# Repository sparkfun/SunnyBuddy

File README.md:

Sunny Buddy - MPPT Solar Charger
================================

[*Sunny Buddy (PRT-12885)*](https://www.sparkfun.com/products/12885)

This is a maximum power point tracking solar charger for single-cell LiPo batteries. 

Repository Contents
-------------------
* **/Fritzing** - Fritzing Example wiring images
* **/Hardware** - All Eagle design files (.brd, .sch)
* **/Production** - Test bed files and production panel files

Documentation
--------------
* **[Hookup Guide](https://learn.sparkfun.com/tutorials/sunny-buddy-solar-charger-v13-hookup-guide)** - Basic hookup guide for the Sunny Buddy.

Product Versions
----------------
* [PRT-12885 ](https://www.sparkfun.com/products/12885 )- Version 1.3
* [PRT-12084](https://www.sparkfun.com/products/12084) - Version 1.0

Version History
---------------
* [v10](https://github.com/sparkfun/SunnyBuddy/tree/HW_V1.0) -GitHub files for v1.0

License Information
-------------------
The hardware is released under [Creative Commons ShareAlike 4.0 International](https://creativecommons.org/licenses/by-sa/4.0/).
The code is beerware; if you see me (or any other SparkFun employee) at the local, and you've found our code helpful, please buy us a round!

Distributed as-is; no warranty is given.

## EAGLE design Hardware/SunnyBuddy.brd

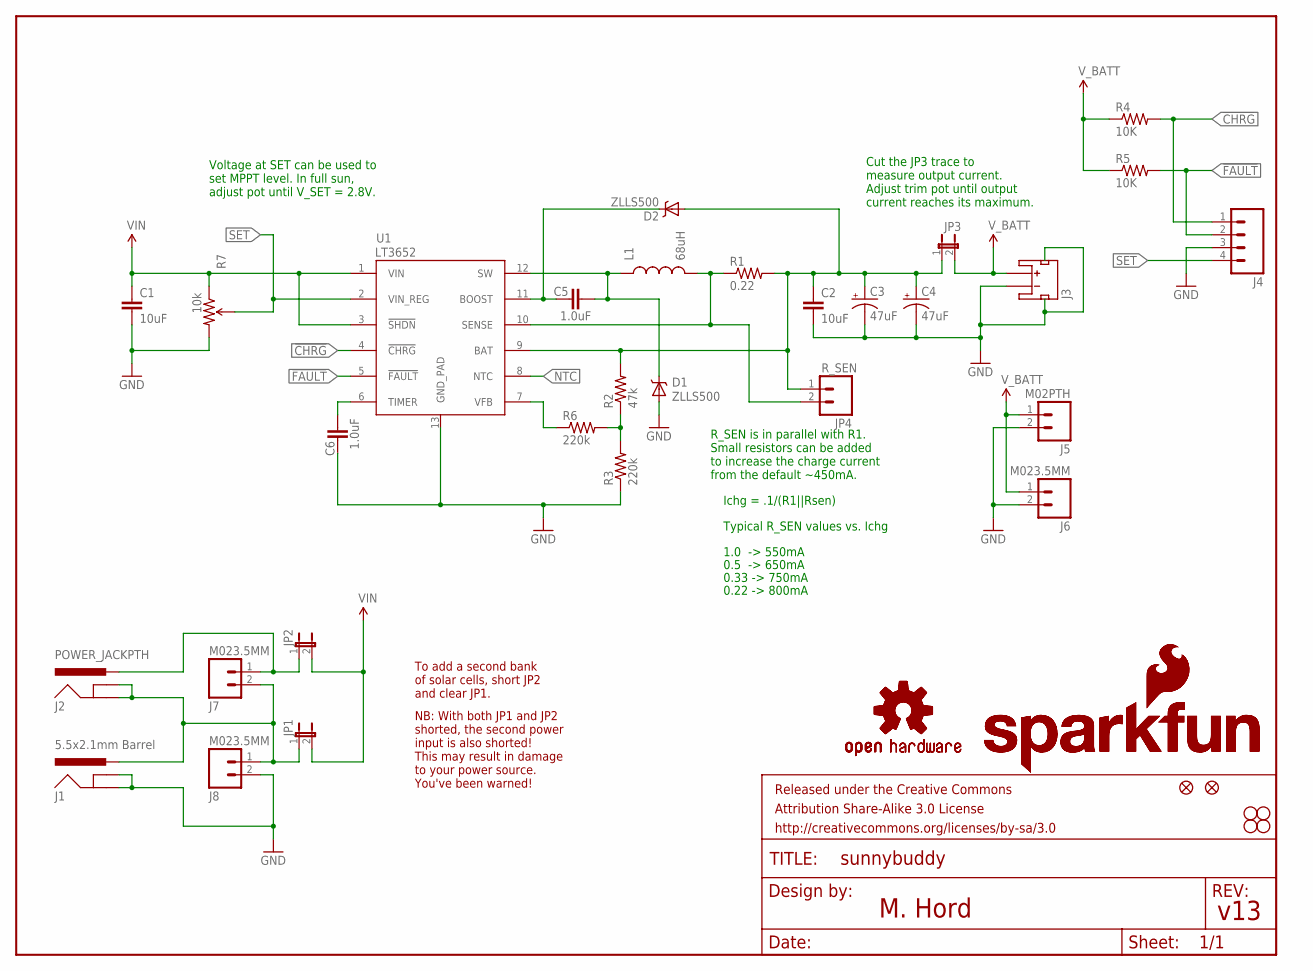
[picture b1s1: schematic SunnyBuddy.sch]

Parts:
C1: 10uF; 1210
C2: 10uF; 1206
C3, C4: 47uF; EIA3528
C5, C6: 1.0uF; 0603-CAP
D1, D2: ZLLS500; SOT23
FID1, FID2: FIDUCIAL1X2; FIDUCIAL-1X2
FRAME1: FRAME-LETTER; CREATIVE_COMMONS
J1: 5.5x2.1mm Barrel; POWER_JACK_SMD
J2: POWER_JACKPTH; POWER_JACK_PTH
J3: JST_2MM_MALE; JST-2-SMD
J4: M04PTH; 1X04
J5: M02PTH; 1X02
J6, J7, J8: M023.5MM; SCREWTERMINAL-3.5MM-2
JP1: JUMPER-2SMD-NC; SJ_2S
JP2: JUMPER-2SMD-NO; SJ_2S-NO
JP3: JUMPER-PTH-2-NC; PTH-JUMPER-NC_BOTTOM_NO_SILK
JP4: R_SEN; 1X02
L1: 68uH; CR75
LOGO1: SFE_LOGO_NAME_FLAME.2_INCH; SFE_LOGO_NAME_FLAME_.2
LOGO2: OSHW-LOGOM; OSHW-LOGO-M
LOGO3: OSHW-LOGOS; OSHW-LOGO-S
LOGO4: SFE_LOGO_NAME_FLAME.3_INCH; SFE_LOGO_NAME_FLAME_.3
R1: 0.22; 0805
R2: 47k; 0603-RES
R3, R6: 220k; 0603-RES
R4, R5: 10K; 0603-RES
R7: 10k; TRIMPOT-3MM
STANDOFF1, STANDOFF2, STANDOFF3, STANDOFF4: STAND-OFF
U1: LT3652; MSOP-12_GND

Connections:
!CHRG: J4.1, R4.2, U1.4 (!CHRG)
!FAULT: J4.2, R5.2, U1.5 (!FAULT)
BOOST: C5.1, D2.3 (C), U1.11 (BOOST)
FB: R2.1, R3.2, R6.2
GND: C1.2, C2.2, C3.C (-), C4.C (-), C6.1, D1.1 (A), J1.GND (GNDBREAK), J1.P$4 (GND), J3.1 (-), J3.NC1 (PAD1), J3.NC2 (PAD2), J4.3, J5.2, J6.2, J8.2, R3.1, R7.3 (CW), U1.13 (GND_PAD)
unnamed: R6.1, U1.7 (VFB)
unnamed: C2.1, C3.A (+), C4.A (+), D2.1 (A), JP3.1, JP4.1, R1.2, R2.2, U1.9 (BAT)
unnamed: J1.VIN0 (PWR), J2.GND, J2.GNDBREAK, J7.2, J8.1, JP1.1
NTC: U1.8 (NTC)
SENSE: JP4.2, L1.P$2 (2), R1.1, U1.10 (SENSE)
SET: J4.4, R7.2 (WIPER), U1.2 (VIN_REG)
SFSASDF: J2.PWR, J7.1, JP2.1
SW: C5.2, D1.3 (C), L1.P$1 (1), U1.12 (SW)
TIMER: C6.2, U1.6 (TIMER)
VIN: C1.1, JP1.2, JP2.2, R7.1 (CCW), U1.1 (VIN), U1.3 (!SHDN)
V_BATT: J3.2 (+), J5.1, J6.1, JP3.2, R4.1, R5.1

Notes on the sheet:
To add a second bank of solar cells, short JP2 and clear JP1.
NB: With both JP1 and JP2 shorted, the second power input is also shorted! This may result in damage to your power source. You've been warned!
v13
M. Hord
Cut the JP3 trace to measure output current. Adjust trim pot until output current reaches its maximum.
R_SEN is in parallel with R1. Small resistors can be added to increase the charge current from the default ~450mA.
0.22 -> 800mA
Ichg = .1/(R1||Rsen)
Typical R_SEN values vs. Ichg
1.0 -> 550mA
0.33 -> 750mA
0.5 -> 650mA
Voltage at SET can be used to set MPPT level. In full sun, adjust pot until V_SET = 2.8V.

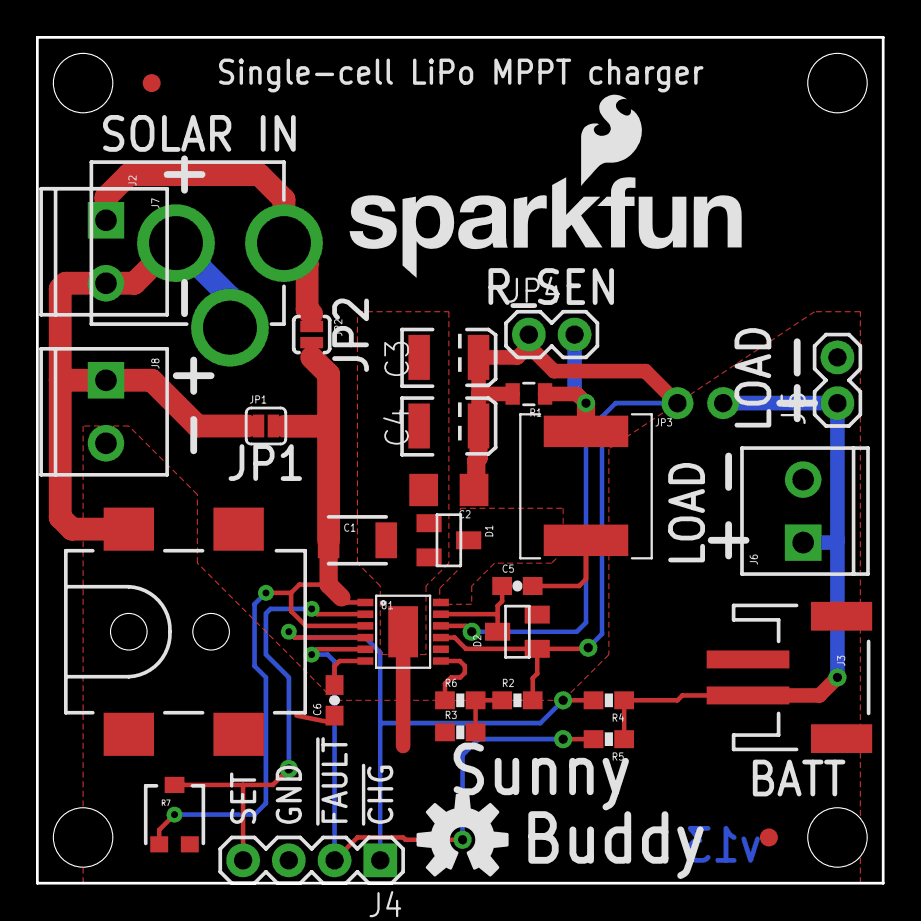
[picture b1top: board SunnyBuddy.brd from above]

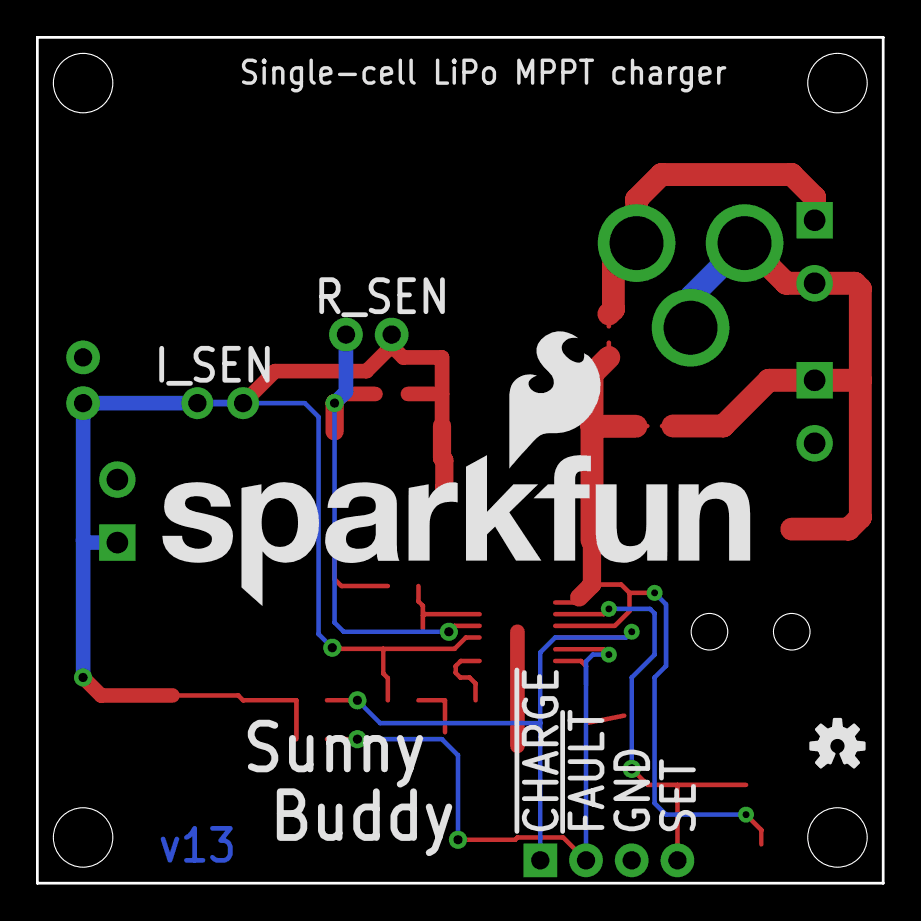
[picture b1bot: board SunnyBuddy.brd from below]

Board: 2 copper layers, 47.0 x 47.0 mm, 40 parts (2 on the bottom side), 15 nets.

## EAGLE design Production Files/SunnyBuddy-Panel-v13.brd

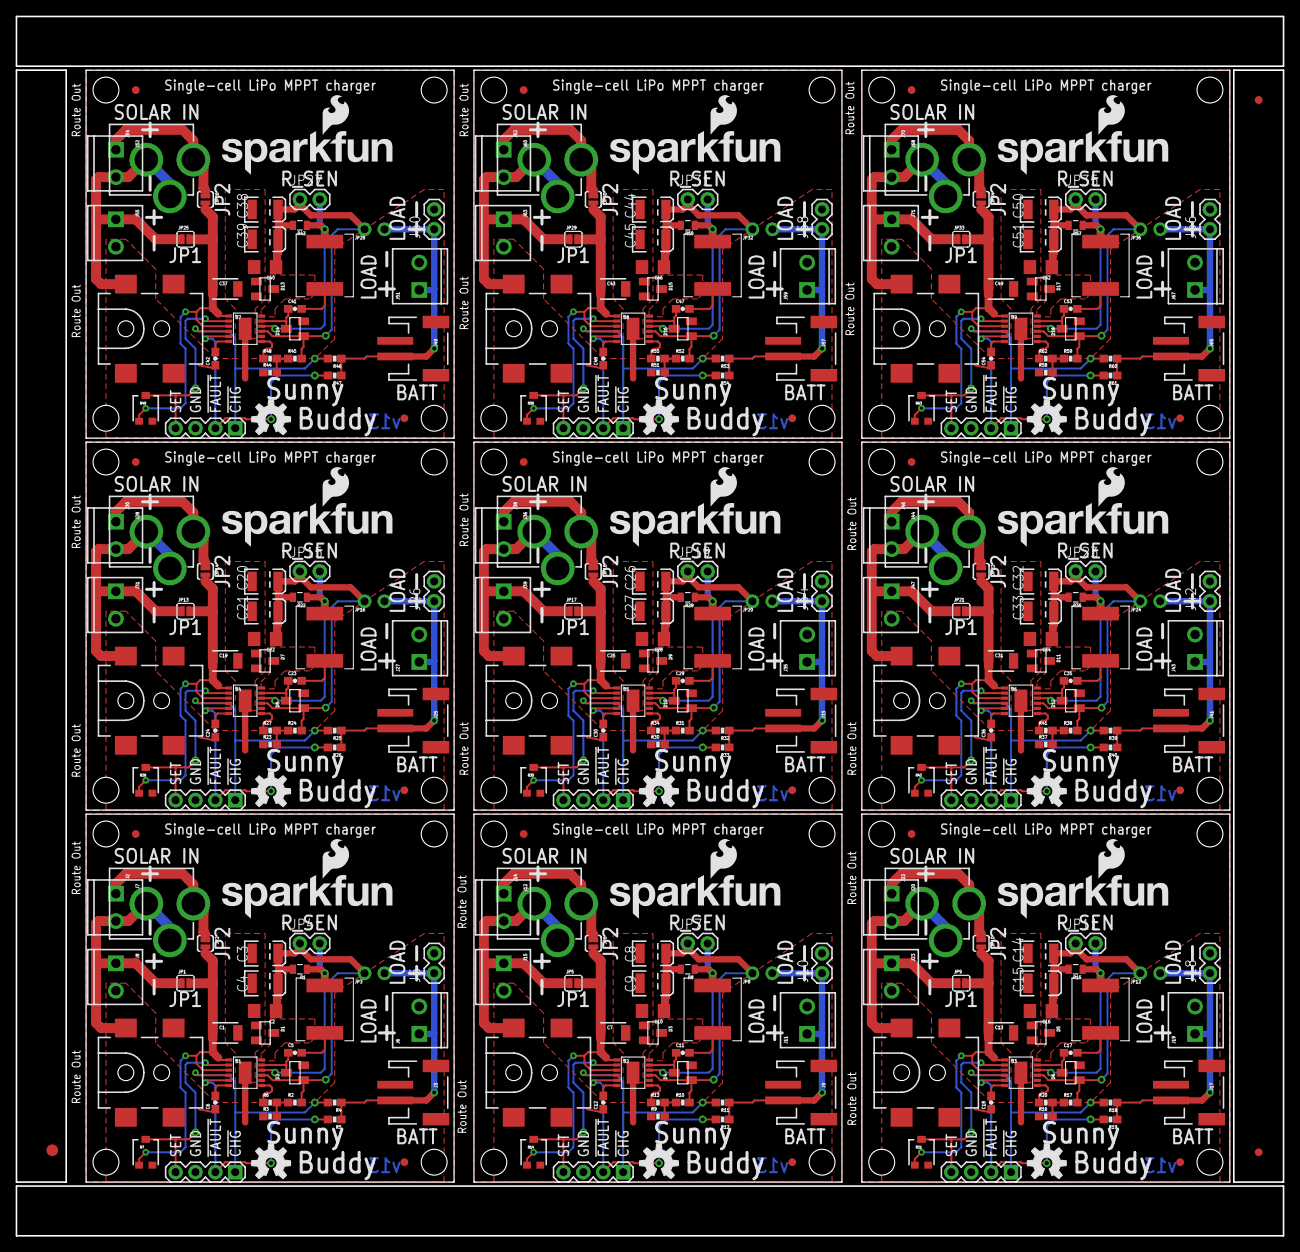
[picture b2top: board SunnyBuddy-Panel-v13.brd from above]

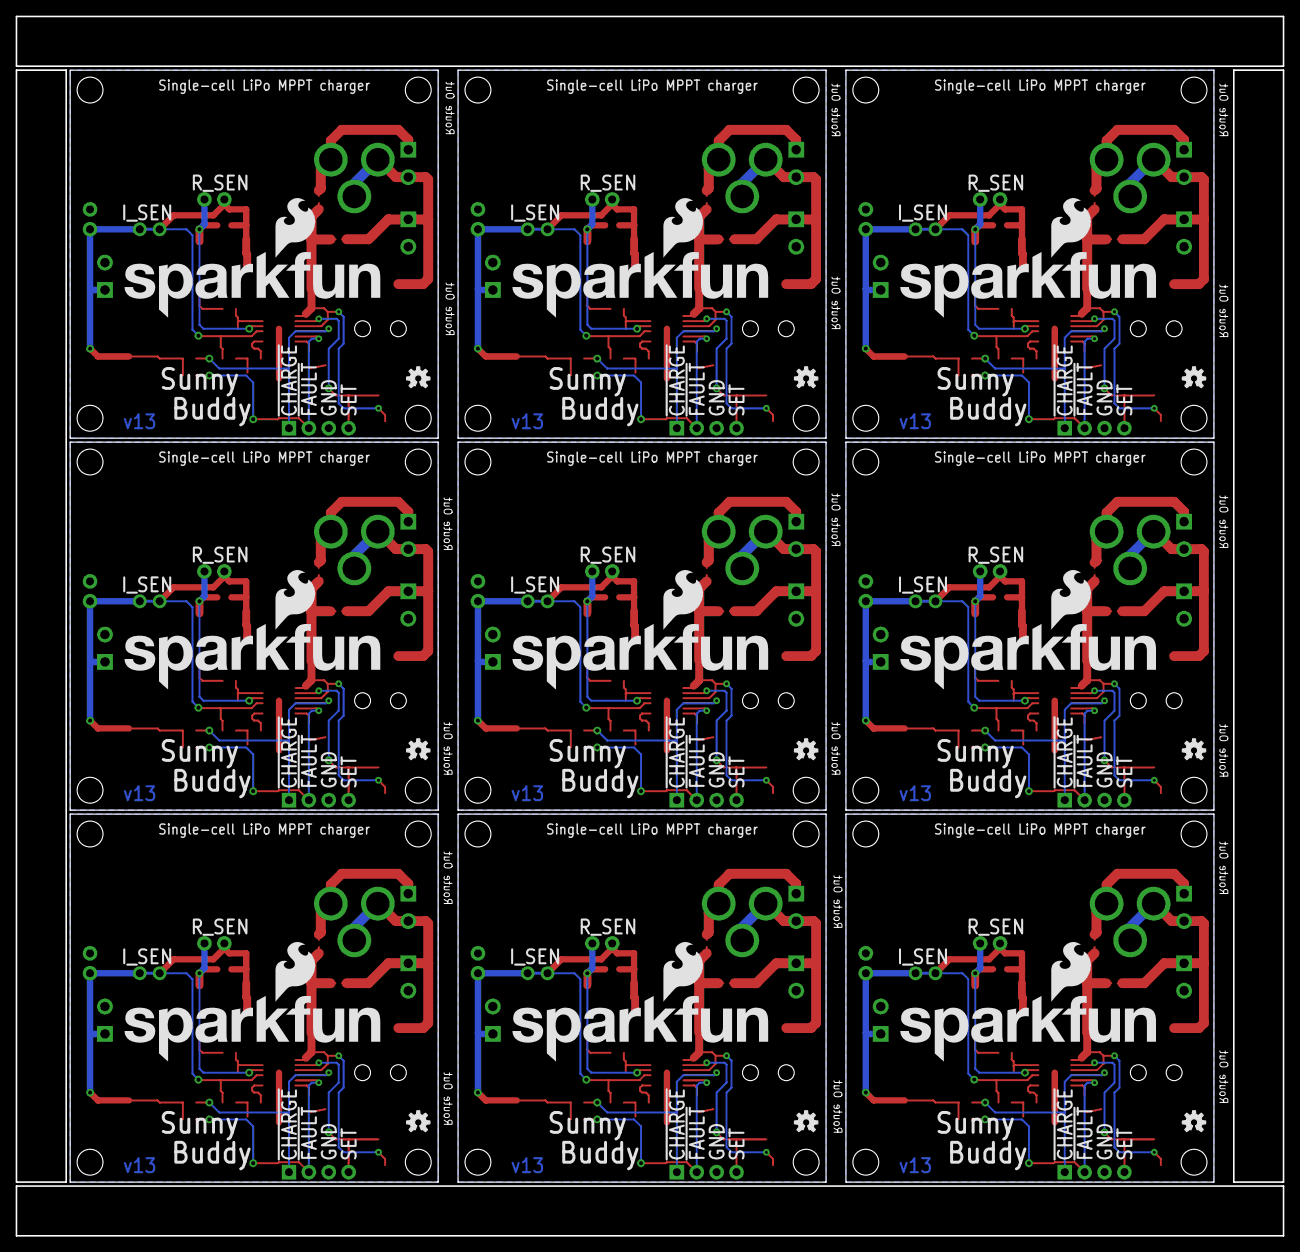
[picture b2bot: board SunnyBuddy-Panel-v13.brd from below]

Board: 2 copper layers, 161.8 x 155.7 mm, 354 parts (18 on the bottom side), 135 nets.

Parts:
C1, C7, C13, C19, C25, C31, C37, C43, C49: 10uF; 1210
C2, C10, C16, C22, C28, C34, C40, C46, C52: 10uF; 1206
C3, C4, C8, C9, C14, C15, C20, C21, C26, C27, C32, C33, C38, C39, C44, C45, C50, C51: 47uF; EIA3528
C5, C6, C11, C12, C17, C18, C23, C24, C29, C30, C35, C36, C41, C42, C47, C48, C53, C54: 1.0uF; 0603-CAP
D1, D2, D3, D4, D5, D6, D7, D8, D9, D10, D11, D12, D13, D14, D15, D16, D17, D18: ZLLS500; SOT23
E$1: FIDUCIAL-1.5X3
E$4, E$6: FIDUCIAL-1X2
FID1, FID2, FID3, FID4, FID5, FID6, FID7, FID8, FID9, FID10, FID11, FID12, FID13, FID14, FID15, FID16, FID17, FID18: FIDUCIAL1X2; FIDUCIAL-1X2
J1, J13, J21, J29, J37, J45, J53, J61, J69: 5.5x2.1mm Barrel; POWER_JACK_SMD
J2, J14, J22, J30, J38, J46, J54, J62, J70: POWER_JACKPTH; POWER_JACK_PTH
J3, J9, J17, J25, J33, J41, J49, J57, J65: JST-2-SMD
J4, J16, J24, J32, J40, J48, J56, J64, J72: 1X04
J5, J10, J18, J26, J34, J42, J50, J58, J66: M02PTH; 1X02
J6, J7, J8, J11, J12, J15, J19, J20, J23, J27, J28, J31, J35, J36, J39, J43, J44, J47, J51, J52, J55, J59, J60, J63, J67, J68, J71: M023.5MM; SCREWTERMINAL-3.5MM-2
JP1, JP5, JP9, JP13, JP17, JP21, JP25, JP29, JP33: SJ_2S
JP2, JP6, JP10, JP14, JP18, JP22, JP26, JP30, JP34: SJ_2S-NO
JP3, JP8, JP12, JP16, JP20, JP24, JP28, JP32, JP36: JUMPER-PTH-2-NC; PTH-JUMPER-NC_BOTTOM_NO_SILK
JP4, JP7, JP11, JP15, JP19, JP23, JP27, JP31, JP35: R_SEN; 1X02
L1, L2, L3, L4, L5, L6, L7, L8, L9: 68uH; CR75
LOGO1, LOGO5, LOGO9, LOGO13, LOGO17, LOGO21, LOGO25, LOGO29, LOGO33: SFE_LOGO_NAME_FLAME.2_INCH; SFE_LOGO_NAME_FLAME_.2
LOGO2, LOGO6, LOGO10, LOGO14, LOGO18, LOGO22, LOGO26, LOGO30, LOGO34: OSHW-LOGOM; OSHW-LOGO-M
LOGO3, LOGO7, LOGO11, LOGO15, LOGO19, LOGO23, LOGO27, LOGO31, LOGO35: OSHW-LOGOS; OSHW-LOGO-S
LOGO4, LOGO8, LOGO12, LOGO16, LOGO20, LOGO24, LOGO28, LOGO32, LOGO36: SFE_LOGO_NAME_FLAME.3_INCH; SFE_LOGO_NAME_FLAME_.3
R1, R8, R15, R22, R29, R36, R43, R50, R57: 0.22; 0805
R2, R10, R17, R24, R31, R38, R45, R52, R59: 47k; 0603-RES
R3, R6, R9, R13, R16, R20, R23, R27, R30, R34, R37, R41, R44, R48, R51, R55, R58, R62: 220k; 0603-RES
R4, R5, R11, R12, R18, R19, R25, R26, R32, R33, R39, R40, R46, R47, R53, R54, R60, R61: 10K; 0603-RES
R7, R14, R21, R28, R35, R42, R49, R56, R63: 10k; TRIMPOT-3MM
STANDOFF1, STANDOFF2, STANDOFF3, STANDOFF4, STANDOFF5, STANDOFF6, STANDOFF7, STANDOFF8, STANDOFF9, STANDOFF10, STANDOFF11, STANDOFF12, STANDOFF13, STANDOFF14, STANDOFF15, STANDOFF16, STANDOFF17, STANDOFF18, STANDOFF19, STANDOFF20, STANDOFF21, STANDOFF22, STANDOFF23, STANDOFF24, STANDOFF25, STANDOFF26, STANDOFF27, STANDOFF28, STANDOFF29, STANDOFF30, STANDOFF31, STANDOFF32, STANDOFF33, STANDOFF34, STANDOFF35, STANDOFF36: STAND-OFF
U1, U2, U3, U4, U5, U6, U7, U8, U9: LT3652; MSOP-12_GND

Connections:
!CHRG: J4.1, R4.2, U1.4
!CHRG1: J16.1, R11.2, U2.4
!CHRG2: J24.1, R18.2, U3.4
!CHRG3: J32.1, R25.2, U4.4
!CHRG4: J40.1, R32.2, U5.4
!CHRG5: J48.1, R39.2, U6.4
!CHRG6: J56.1, R46.2, U7.4
!CHRG7: J64.1, R53.2, U8.4
!CHRG8: J72.1, R60.2, U9.4
!FAULT: J4.2, R5.2, U1.5
!FAULT1: J16.2, R12.2, U2.5
!FAULT2: J24.2, R19.2, U3.5
!FAULT3: J32.2, R26.2, U4.5
!FAULT4: J40.2, R33.2, U5.5
!FAULT5: J48.2, R40.2, U6.5
!FAULT6: J56.2, R47.2, U7.5
!FAULT7: J64.2, R54.2, U8.5
!FAULT8: J72.2, R61.2, U9.5
BOOST: C5.1, D2.3, U1.11
BOOST1: C11.1, D4.3, U2.11
BOOST2: C17.1, D6.3, U3.11
BOOST3: C23.1, D8.3, U4.11
BOOST4: C29.1, D10.3, U5.11
BOOST5: C35.1, D12.3, U6.11
BOOST6: C41.1, D14.3, U7.11
BOOST7: C47.1, D16.3, U8.11
BOOST8: C53.1, D18.3, U9.11
FB: R2.1, R3.2, R6.2
FB1: R9.2, R10.1, R13.2
FB2: R16.2, R17.1, R20.2
FB3: R23.2, R24.1, R27.2
FB4: R30.2, R31.1, R34.2
FB5: R37.2, R38.1, R41.2
FB6: R44.2, R45.1, R48.2
FB7: R51.2, R52.1, R55.2
FB8: R58.2, R59.1, R62.2
GND: C1.2, C2.2, C3.C, C4.C, C6.1, D1.1, J1.GND, J1.P$4, J3.1, J3.NC1, J3.NC2, J4.3, J5.2, J6.2, J8.2, R3.1, R7.3, U1.13
GND1: C7.2, C8.C, C9.C, C10.2, C12.1, D3.1, J9.1, J9.NC1, J9.NC2, J10.2, J11.2, J13.GND, J13.P$4, J15.2, J16.3, R9.1, R14.3, U2.13
GND2: C13.2, C14.C, C15.C, C16.2, C18.1, D5.1, J17.1, J17.NC1, J17.NC2, J18.2, J19.2, J21.GND, J21.P$4, J23.2, J24.3, R16.1, R21.3, U3.13
GND3: C19.2, C20.C, C21.C, C22.2, C24.1, D7.1, J25.1, J25.NC1, J25.NC2, J26.2, J27.2, J29.GND, J29.P$4, J31.2, J32.3, R23.1, R28.3, U4.13
GND4: C25.2, C26.C, C27.C, C28.2, C30.1, D9.1, J33.1, J33.NC1, J33.NC2, J34.2, J35.2, J37.GND, J37.P$4, J39.2, J40.3, R30.1, R35.3, U5.13
GND5: C31.2, C32.C, C33.C, C34.2, C36.1, D11.1, J41.1, J41.NC1, J41.NC2, J42.2, J43.2, J45.GND, J45.P$4, J47.2, J48.3, R37.1, R42.3, U6.13
GND6: C37.2, C38.C, C39.C, C40.2, C42.1, D13.1, J49.1, J49.NC1, J49.NC2, J50.2, J51.2, J53.GND, J53.P$4, J55.2, J56.3, R44.1, R49.3, U7.13
GND7: C43.2, C44.C, C45.C, C46.2, C48.1, D15.1, J57.1, J57.NC1, J57.NC2, J58.2, J59.2, J61.GND, J61.P$4, J63.2, J64.3, R51.1, R56.3, U8.13
GND8: C49.2, C50.C, C51.C, C52.2, C54.1, D17.1, J65.1, J65.NC1, J65.NC2, J66.2, J67.2, J69.GND, J69.P$4, J71.2, J72.3, R58.1, R63.3, U9.13
unnamed: R6.1, U1.7
unnamed: C2.1, C3.A, C4.A, D2.1, JP3.1, JP4.1, R1.2, R2.2, U1.9
unnamed: J12.2, J13.VIN0, J14.GND, J14.GNDBREAK, J15.1, JP5.1
unnamed: J1.VIN0, J2.GND, J2.GNDBREAK, J7.2, J8.1, JP1.1
unnamed: R13.1, U2.7
unnamed: C8.A, C9.A, C10.1, D4.1, JP7.1, JP8.1, R8.2, R10.2, U2.9
unnamed: J20.2, J21.VIN0, J22.GND, J22.GNDBREAK, J23.1, JP9.1
unnamed: R20.1, U3.7
unnamed: C14.A, C15.A, C16.1, D6.1, JP11.1, JP12.1, R15.2, R17.2, U3.9
unnamed: J28.2, J29.VIN0, J30.GND, J30.GNDBREAK, J31.1, JP13.1
unnamed: R27.1, U4.7
unnamed: C20.A, C21.A, C22.1, D8.1, JP15.1, JP16.1, R22.2, R24.2, U4.9
unnamed: J36.2, J37.VIN0, J38.GND, J38.GNDBREAK, J39.1, JP17.1
unnamed: R34.1, U5.7
unnamed: C26.A, C27.A, C28.1, D10.1, JP19.1, JP20.1, R29.2, R31.2, U5.9
unnamed: J44.2, J45.VIN0, J46.GND, J46.GNDBREAK, J47.1, JP21.1
unnamed: R41.1, U6.7
unnamed: C32.A, C33.A, C34.1, D12.1, JP23.1, JP24.1, R36.2, R38.2, U6.9
unnamed: J52.2, J53.VIN0, J54.GND, J54.GNDBREAK, J55.1, JP25.1
unnamed: R48.1, U7.7
unnamed: C38.A, C39.A, C40.1, D14.1, JP27.1, JP28.1, R43.2, R45.2, U7.9
unnamed: J60.2, J61.VIN0, J62.GND, J62.GNDBREAK, J63.1, JP29.1
unnamed: R55.1, U8.7
unnamed: C44.A, C45.A, C46.1, D16.1, JP31.1, JP32.1, R50.2, R52.2, U8.9
unnamed: J68.2, J69.VIN0, J70.GND, J70.GNDBREAK, J71.1, JP33.1
unnamed: R62.1, U9.7
unnamed: C50.A, C51.A, C52.1, D18.1, JP35.1, JP36.1, R57.2, R59.2, U9.9
SENSE: JP4.2, L1.P$2, R1.1, U1.10
SENSE1: JP7.2, L2.P$2, R8.1, U2.10
SENSE2: JP11.2, L3.P$2, R15.1, U3.10
SENSE3: JP15.2, L4.P$2, R22.1, U4.10
SENSE4: JP19.2, L5.P$2, R29.1, U5.10
SENSE5: JP23.2, L6.P$2, R36.1, U6.10
SENSE6: JP27.2, L7.P$2, R43.1, U7.10
SENSE7: JP31.2, L8.P$2, R50.1, U8.10
SENSE8: JP35.2, L9.P$2, R57.1, U9.10
SET: J4.4, R7.2, U1.2
SET1: J16.4, R14.2, U2.2
SET2: J24.4, R21.2, U3.2
SET3: J32.4, R28.2, U4.2
SET4: J40.4, R35.2, U5.2
SET5: J48.4, R42.2, U6.2
SET6: J56.4, R49.2, U7.2
SET7: J64.4, R56.2, U8.2
SET8: J72.4, R63.2, U9.2
SFSASDF: J2.PWR, J7.1, JP2.1
SFSASDF1: J12.1, J14.PWR, JP6.1
SFSASDF2: J20.1, J22.PWR, JP10.1
SFSASDF3: J28.1, J30.PWR, JP14.1
SFSASDF4: J36.1, J38.PWR, JP18.1
SFSASDF5: J44.1, J46.PWR, JP22.1
SFSASDF6: J52.1, J54.PWR, JP26.1
SFSASDF7: J60.1, J62.PWR, JP30.1
SFSASDF8: J68.1, J70.PWR, JP34.1
SW: C5.2, D1.3, L1.P$1, U1.12
SW1: C11.2, D3.3, L2.P$1, U2.12
SW2: C17.2, D5.3, L3.P$1, U3.12
SW3: C23.2, D7.3, L4.P$1, U4.12
SW4: C29.2, D9.3, L5.P$1, U5.12
SW5: C35.2, D11.3, L6.P$1, U6.12
SW6: C41.2, D13.3, L7.P$1, U7.12
SW7: C47.2, D15.3, L8.P$1, U8.12
SW8: C53.2, D17.3, L9.P$1, U9.12
TIMER: C6.2, U1.6
TIMER1: C12.2, U2.6
TIMER2: C18.2, U3.6
TIMER3: C24.2, U4.6
TIMER4: C30.2, U5.6
TIMER5: C36.2, U6.6
TIMER6: C42.2, U7.6
TIMER7: C48.2, U8.6
TIMER8: C54.2, U9.6
VIN: C1.1, JP1.2, JP2.2, R7.1, U1.1, U1.3
VIN1: C7.1, JP5.2, JP6.2, R14.1, U2.1, U2.3
VIN2: C13.1, JP9.2, JP10.2, R21.1, U3.1, U3.3
VIN3: C19.1, JP13.2, JP14.2, R28.1, U4.1, U4.3
VIN4: C25.1, JP17.2, JP18.2, R35.1, U5.1, U5.3
VIN5: C31.1, JP21.2, JP22.2, R42.1, U6.1, U6.3
VIN6: C37.1, JP25.2, JP26.2, R49.1, U7.1, U7.3
VIN7: C43.1, JP29.2, JP30.2, R56.1, U8.1, U8.3
VIN8: C49.1, JP33.2, JP34.2, R63.1, U9.1, U9.3
V_BATT: J3.2, J5.1, J6.1, JP3.2, R4.1, R5.1
V_BATT1: J9.2, J10.1, J11.1, JP8.2, R11.1, R12.1
V_BATT2: J17.2, J18.1, J19.1, JP12.2, R18.1, R19.1
V_BATT3: J25.2, J26.1, J27.1, JP16.2, R25.1, R26.1
V_BATT4: J33.2, J34.1, J35.1, JP20.2, R32.1, R33.1
V_BATT5: J41.2, J42.1, J43.1, JP24.2, R39.1, R40.1
V_BATT6: J49.2, J50.1, J51.1, JP28.2, R46.1, R47.1
V_BATT7: J57.2, J58.1, J59.1, JP32.2, R53.1, R54.1
V_BATT8: J65.2, J66.1, J67.1, JP36.2, R60.1, R61.1

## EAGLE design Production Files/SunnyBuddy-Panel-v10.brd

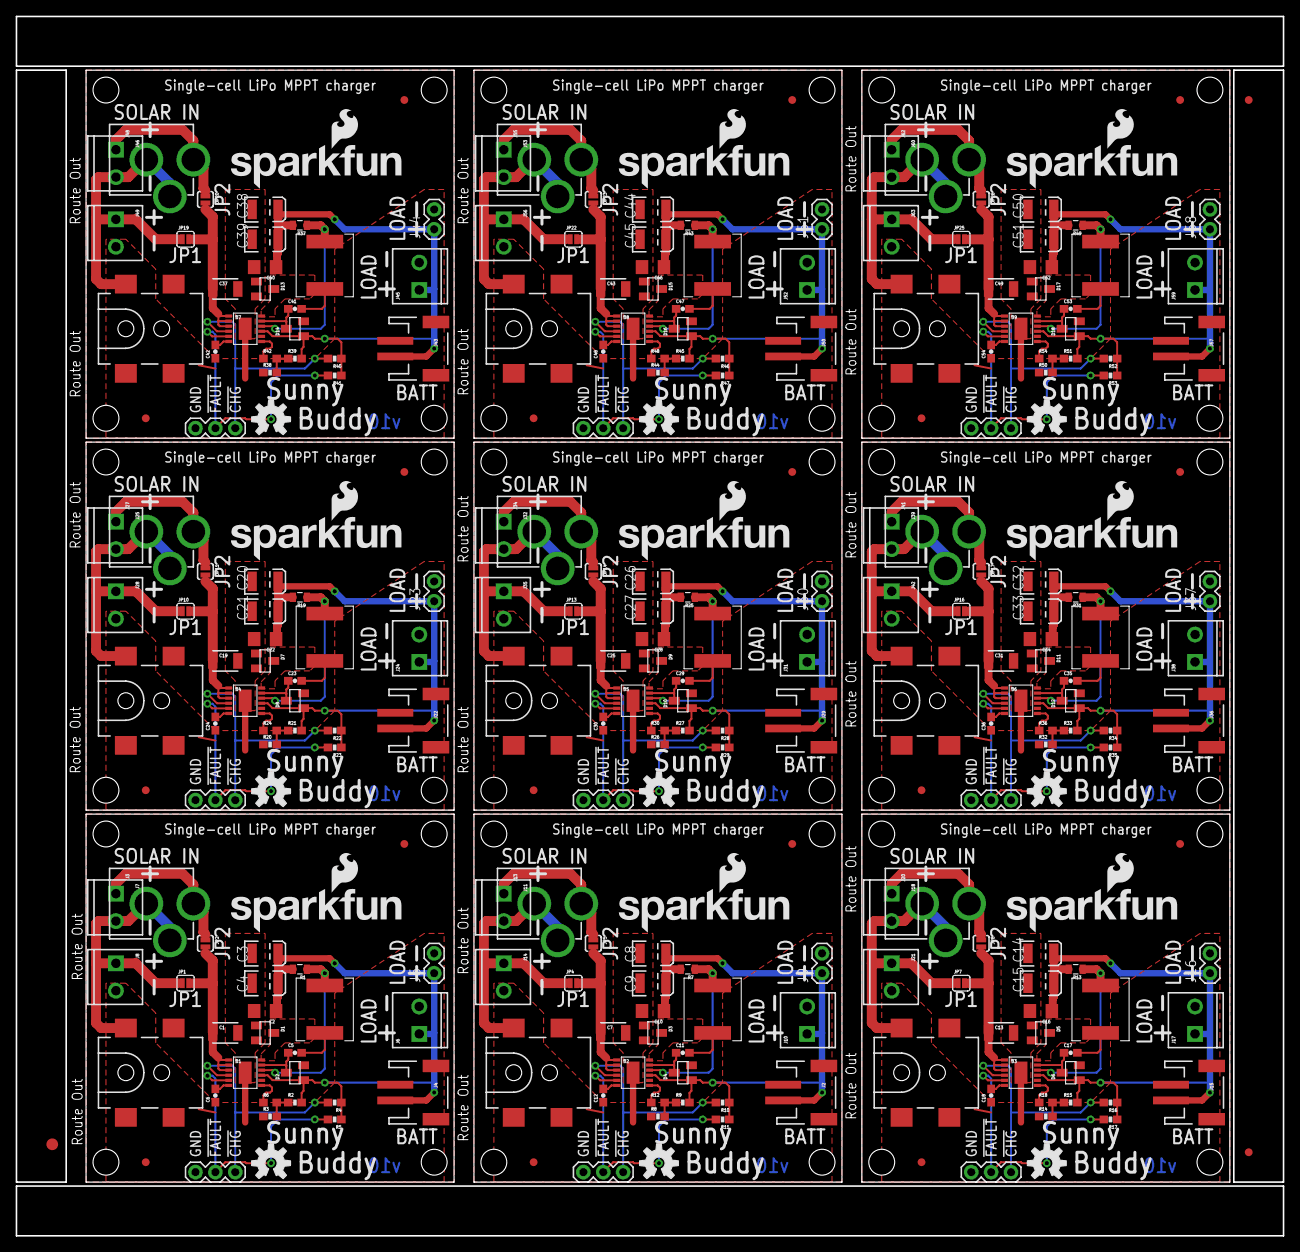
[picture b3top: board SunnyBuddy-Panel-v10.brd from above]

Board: 2 copper layers, 161.8 x 155.7 mm, 309 parts (0 on the bottom side), 117 nets.

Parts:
C1, C7, C13, C19, C25, C31, C37, C43, C49: 10uF; 1210
C2, C10, C16, C22, C28, C34, C40, C46, C52: 10uF; 1206
C3, C4, C8, C9, C14, C15, C20, C21, C26, C27, C32, C33, C38, C39, C44, C45, C50, C51: 47uF; EIA3528
C5, C6, C11, C12, C17, C18, C23, C24, C29, C30, C35, C36, C41, C42, C47, C48, C53, C54: 1.0uF; 0603-CAP
D1, D2, D3, D4, D5, D6, D7, D8, D9, D10, D11, D12, D13, D14, D15, D16, D17, D18: ZLLS500; SOT23
E$1: FIDUCIAL-1.5X3
E$5, E$7: FIDUCIAL-1X2
FID1, FID2, FID3, FID4, FID5, FID6, FID7, FID8, FID9, FID10, FID11, FID12, FID13, FID14, FID15, FID16, FID17, FID18: FIDUCIAL1X2; FIDUCIAL-1X2
J1, J12, J19, J26, J33, J40, J47, J54, J61: 5.5x2.1mm Barrel; POWER_JACK_SMD
J2, J4, J15, J22, J29, J36, J43, J50, J57: JST-2-SMD
J3, J13, J20, J27, J34, J41, J48, J55, J62: POWER_JACKPTH; POWER_JACK_PTH
J5, J9, J16, J23, J30, J37, J44, J51, J58: M02PTH; 1X02
J6, J7, J8, J10, J11, J14, J17, J18, J21, J24, J25, J28, J31, J32, J35, J38, J39, J42, J45, J46, J49, J52, J53, J56, J59, J60, J63: M023.5MM; SCREWTERMINAL-3.5MM-2
JP1, JP4, JP7, JP10, JP13, JP16, JP19, JP22, JP25: SJ_2S
JP2, JP5, JP8, JP11, JP14, JP17, JP20, JP23, JP26: SJ_2S-NO
JP3, JP6, JP9, JP12, JP15, JP18, JP21, JP24, JP27: 1X03
L1, L2, L3, L4, L5, L6, L7, L8, L9: 68uH; CR75
LOGO1, LOGO3, LOGO5, LOGO7, LOGO9, LOGO11, LOGO13, LOGO15, LOGO17: SFE_LOGO_NAME_FLAME.2_INCH; SFE_LOGO_NAME_FLAME_.2
LOGO2, LOGO4, LOGO6, LOGO8, LOGO10, LOGO12, LOGO14, LOGO16, LOGO18: OSHW-LOGOM; OSHW-LOGO-M
R1, R7, R13, R19, R25, R31, R37, R43, R49: 0.22; 0805
R2, R9, R15, R21, R27, R33, R39, R45, R51: 100k; 0603-RES
R3, R8, R14, R20, R26, R32, R38, R44, R50: 300k; 0603-RES
R4, R5, R10, R11, R16, R17, R22, R23, R28, R29, R34, R35, R40, R41, R46, R47, R52, R53: 10K; 0603-RES
R6, R12, R18, R24, R30, R36, R42, R48, R54: 0; 0603
STANDOFF1, STANDOFF2, STANDOFF3, STANDOFF4, STANDOFF5, STANDOFF6, STANDOFF7, STANDOFF8, STANDOFF9, STANDOFF10, STANDOFF11, STANDOFF12, STANDOFF13, STANDOFF14, STANDOFF15, STANDOFF16, STANDOFF17, STANDOFF18, STANDOFF19, STANDOFF20, STANDOFF21, STANDOFF22, STANDOFF23, STANDOFF24, STANDOFF25, STANDOFF26, STANDOFF27, STANDOFF28, STANDOFF29, STANDOFF30, STANDOFF31, STANDOFF32, STANDOFF33, STANDOFF34, STANDOFF35, STANDOFF36: STAND-OFF
U1, U2, U3, U4, U5, U6, U7, U8, U9: LT3652; MSOP-12_GND

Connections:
!CHRG: JP3.1, R4.2, U1.4
!CHRG1: JP6.1, R10.2, U2.4
!CHRG2: JP9.1, R16.2, U3.4
!CHRG3: JP12.1, R22.2, U4.4
!CHRG4: JP15.1, R28.2, U5.4
!CHRG5: JP18.1, R34.2, U6.4
!CHRG6: JP21.1, R40.2, U7.4
!CHRG7: JP24.1, R46.2, U8.4
!CHRG8: JP27.1, R52.2, U9.4
!FAULT: JP3.2, R5.2, U1.5
!FAULT1: JP6.2, R11.2, U2.5
!FAULT2: JP9.2, R17.2, U3.5
!FAULT3: JP12.2, R23.2, U4.5
!FAULT4: JP15.2, R29.2, U5.5
!FAULT5: JP18.2, R35.2, U6.5
!FAULT6: JP21.2, R41.2, U7.5
!FAULT7: JP24.2, R47.2, U8.5
!FAULT8: JP27.2, R53.2, U9.5
BOOST: C5.1, D2.3, U1.11
BOOST1: C11.1, D4.3, U2.11
BOOST2: C17.1, D6.3, U3.11
BOOST3: C23.1, D8.3, U4.11
BOOST4: C29.1, D10.3, U5.11
BOOST5: C35.1, D12.3, U6.11
BOOST6: C41.1, D14.3, U7.11
BOOST7: C47.1, D16.3, U8.11
BOOST8: C53.1, D18.3, U9.11
FB: R2.1, R3.2, R6.2
FB1: R8.2, R9.1, R12.2
FB2: R14.2, R15.1, R18.2
FB3: R20.2, R21.1, R24.2
FB4: R26.2, R27.1, R30.2
FB5: R32.2, R33.1, R36.2
FB6: R38.2, R39.1, R42.2
FB7: R44.2, R45.1, R48.2
FB8: R50.2, R51.1, R54.2
GND: C1.2, C2.2, C3.C, C4.C, C6.1, D1.1, J1.GND, J1.P$4, J4.1, J4.NC1, J4.NC2, J5.2, J6.2, J8.2, JP3.3, R3.1, U1.13
GND1: C7.2, C8.C, C9.C, C10.2, C12.1, D3.1, J2.1, J2.NC1, J2.NC2, J9.2, J10.2, J12.GND, J12.P$4, J14.2, JP6.3, R8.1, U2.13
GND2: C13.2, C14.C, C15.C, C16.2, C18.1, D5.1, J15.1, J15.NC1, J15.NC2, J16.2, J17.2, J19.GND, J19.P$4, J21.2, JP9.3, R14.1, U3.13
GND3: C19.2, C20.C, C21.C, C22.2, C24.1, D7.1, J22.1, J22.NC1, J22.NC2, J23.2, J24.2, J26.GND, J26.P$4, J28.2, JP12.3, R20.1, U4.13
GND4: C25.2, C26.C, C27.C, C28.2, C30.1, D9.1, J29.1, J29.NC1, J29.NC2, J30.2, J31.2, J33.GND, J33.P$4, J35.2, JP15.3, R26.1, U5.13
GND5: C31.2, C32.C, C33.C, C34.2, C36.1, D11.1, J36.1, J36.NC1, J36.NC2, J37.2, J38.2, J40.GND, J40.P$4, J42.2, JP18.3, R32.1, U6.13
GND6: C37.2, C38.C, C39.C, C40.2, C42.1, D13.1, J43.1, J43.NC1, J43.NC2, J44.2, J45.2, J47.GND, J47.P$4, J49.2, JP21.3, R38.1, U7.13
GND7: C43.2, C44.C, C45.C, C46.2, C48.1, D15.1, J50.1, J50.NC1, J50.NC2, J51.2, J52.2, J54.GND, J54.P$4, J56.2, JP24.3, R44.1, U8.13
GND8: C49.2, C50.C, C51.C, C52.2, C54.1, D17.1, J57.1, J57.NC1, J57.NC2, J58.2, J59.2, J61.GND, J61.P$4, J63.2, JP27.3, R50.1, U9.13
unnamed: R6.1, U1.7
unnamed: J11.2, J12.VIN0, J13.GND, J13.GNDBREAK, J14.1, JP4.1
unnamed: R12.1, U2.7
unnamed: J1.VIN0, J3.GND, J3.GNDBREAK, J7.2, J8.1, JP1.1
unnamed: J18.2, J19.VIN0, J20.GND, J20.GNDBREAK, J21.1, JP7.1
unnamed: R18.1, U3.7
unnamed: J25.2, J26.VIN0, J27.GND, J27.GNDBREAK, J28.1, JP10.1
unnamed: R24.1, U4.7
unnamed: J32.2, J33.VIN0, J34.GND, J34.GNDBREAK, J35.1, JP13.1
unnamed: R30.1, U5.7
unnamed: J39.2, J40.VIN0, J41.GND, J41.GNDBREAK, J42.1, JP16.1
unnamed: R36.1, U6.7
unnamed: J46.2, J47.VIN0, J48.GND, J48.GNDBREAK, J49.1, JP19.1
unnamed: R42.1, U7.7
unnamed: J53.2, J54.VIN0, J55.GND, J55.GNDBREAK, J56.1, JP22.1
unnamed: R48.1, U8.7
unnamed: J60.2, J61.VIN0, J62.GND, J62.GNDBREAK, J63.1, JP25.1
unnamed: R54.1, U9.7
SENSE: L1.P$2, R1.1, U1.10
SENSE1: L2.P$2, R7.1, U2.10
SENSE2: L3.P$2, R13.1, U3.10
SENSE3: L4.P$2, R19.1, U4.10
SENSE4: L5.P$2, R25.1, U5.10
SENSE5: L6.P$2, R31.1, U6.10
SENSE6: L7.P$2, R37.1, U7.10
SENSE7: L8.P$2, R43.1, U8.10
SENSE8: L9.P$2, R49.1, U9.10
SFSASDF: J3.PWR, J7.1, JP2.1
SFSASDF1: J11.1, J13.PWR, JP5.1
SFSASDF2: J18.1, J20.PWR, JP8.1
SFSASDF3: J25.1, J27.PWR, JP11.1
SFSASDF4: J32.1, J34.PWR, JP14.1
SFSASDF5: J39.1, J41.PWR, JP17.1
SFSASDF6: J46.1, J48.PWR, JP20.1
SFSASDF7: J53.1, J55.PWR, JP23.1
SFSASDF8: J60.1, J62.PWR, JP26.1
SW: C5.2, D1.3, L1.P$1, U1.12
SW1: C11.2, D3.3, L2.P$1, U2.12
SW2: C17.2, D5.3, L3.P$1, U3.12
SW3: C23.2, D7.3, L4.P$1, U4.12
SW4: C29.2, D9.3, L5.P$1, U5.12
SW5: C35.2, D11.3, L6.P$1, U6.12
SW6: C41.2, D13.3, L7.P$1, U7.12
SW7: C47.2, D15.3, L8.P$1, U8.12
SW8: C53.2, D17.3, L9.P$1, U9.12
TIMER: C6.2, U1.6
TIMER1: C12.2, U2.6
TIMER2: C18.2, U3.6
TIMER3: C24.2, U4.6
TIMER4: C30.2, U5.6
TIMER5: C36.2, U6.6
TIMER6: C42.2, U7.6
TIMER7: C48.2, U8.6
TIMER8: C54.2, U9.6
VIN: C1.1, JP1.2, JP2.2, U1.1, U1.2, U1.3
VIN1: C7.1, JP4.2, JP5.2, U2.1, U2.2, U2.3
VIN2: C13.1, JP7.2, JP8.2, U3.1, U3.2, U3.3
VIN3: C19.1, JP10.2, JP11.2, U4.1, U4.2, U4.3
VIN4: C25.1, JP13.2, JP14.2, U5.1, U5.2, U5.3
VIN5: C31.1, JP16.2, JP17.2, U6.1, U6.2, U6.3
VIN6: C37.1, JP19.2, JP20.2, U7.1, U7.2, U7.3
VIN7: C43.1, JP22.2, JP23.2, U8.1, U8.2, U8.3
VIN8: C49.1, JP25.2, JP26.2, U9.1, U9.2, U9.3
V_BATT: C2.1, C3.A, C4.A, D2.1, J4.2, J5.1, J6.1, R1.2, R2.2, R4.1, R5.1, U1.9
V_BATT1: C8.A, C9.A, C10.1, D4.1, J2.2, J9.1, J10.1, R7.2, R9.2, R10.1, R11.1, U2.9
V_BATT2: C14.A, C15.A, C16.1, D6.1, J15.2, J16.1, J17.1, R13.2, R15.2, R16.1, R17.1, U3.9
V_BATT3: C20.A, C21.A, C22.1, D8.1, J22.2, J23.1, J24.1, R19.2, R21.2, R22.1, R23.1, U4.9
V_BATT4: C26.A, C27.A, C28.1, D10.1, J29.2, J30.1, J31.1, R25.2, R27.2, R28.1, R29.1, U5.9
V_BATT5: C32.A, C33.A, C34.1, D12.1, J36.2, J37.1, J38.1, R31.2, R33.2, R34.1, R35.1, U6.9
V_BATT6: C38.A, C39.A, C40.1, D14.1, J43.2, J44.1, J45.1, R37.2, R39.2, R40.1, R41.1, U7.9
V_BATT7: C44.A, C45.A, C46.1, D16.1, J50.2, J51.1, J52.1, R43.2, R45.2, R46.1, R47.1, U8.9
V_BATT8: C50.A, C51.A, C52.1, D18.1, J57.2, J58.1, J59.1, R49.2, R51.2, R52.1, R53.1, U9.9

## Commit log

2013-08-14 Proto commit
2013-12-04 New inductor, better fb, add CHG and FLT
2013-12-04 Change version numbers
2014-01-08 Release to reds, chg v#, move 1 via, add pol silk
2014-01-21 Added local board fiducials
2014-01-21 created panel
2014-04-09 Updating README for release
2014-04-09 Update README.md
    Adding product link.
2014-04-25 Add trimpot, adjust output res values
2014-05-07 Change 10th vias to 15th
2014-05-22 Add current sense jumper, set V node, Fritzing
2014-06-24 Changes to silk, only, for production
2014-06-26 added board fiducials
2014-06-26 created panel v13
2014-06-26 added route out instructions to panel
2014-11-03 Fixing brd file merge conflicts

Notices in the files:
parts and their libraries:
SparkFun-Aesthetics: Licensing: CC v3.0 Share-Alike You are welcome to use this library for commercial purposes.
SparkFun-Aesthetics: Released under the Creative Commons Attribution Share-Alike 3.0 License
SparkFun-Aesthetics: http://creativecommons.org/licenses/by-sa/3.0
